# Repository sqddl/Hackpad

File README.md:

# Hackpad

### Overview
This hackpad is meant to be used for convience hence the layout of 4 keys per row. Making it ideal to rest your hand on it.
I wanted to make this so I can have specific keys for different functions for my computer.

BOM:
- 8x Cherry MX Switches
- 8x Blank DSA Keycaps
- 1x XIAO RP2040
- 4x M3x16 Screws
- 3D Printed Case (2 Parts)

| PCB | Schematics | Case |
|-----|------------|------|
|||

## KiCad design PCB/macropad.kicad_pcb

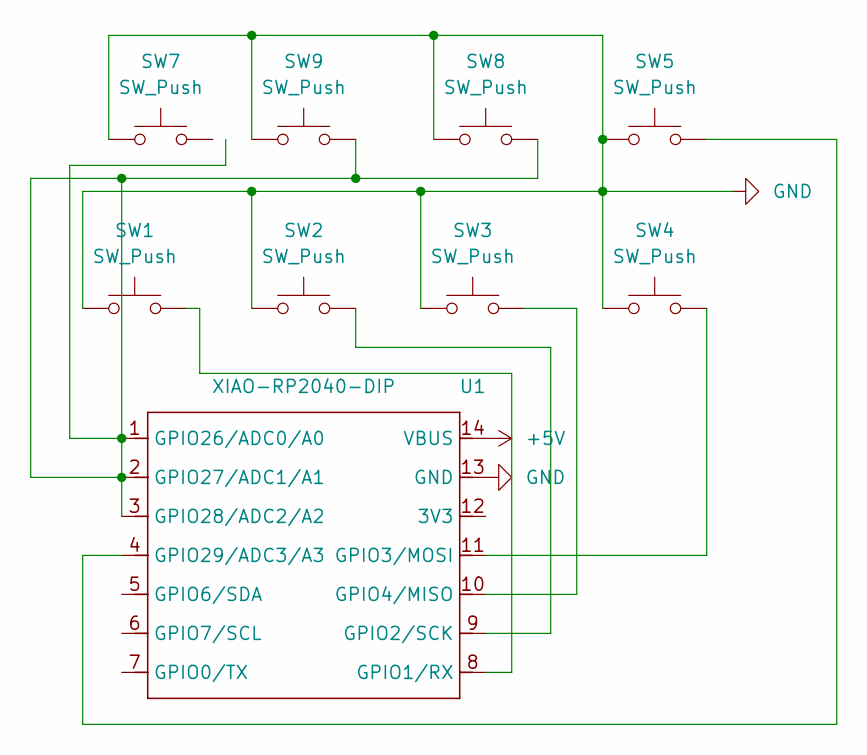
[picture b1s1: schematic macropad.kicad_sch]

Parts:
SW1, SW2, SW3, SW4, SW5, SW7, SW8, SW9: SW_Push; SW_Cherry_MX_1.00u_PCB
U1: XIAO-RP2040-DIP

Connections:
+5V: U1.14 (VBUS)
GND: SW1.1, SW2.1, SW3.1, SW4.1, SW5.1, SW7.1, SW8.1, SW9.1, U1.13 (GND)
unnamed: SW1.2, U1.8 (GPIO1/RX)
unnamed: SW2.2, U1.9 (GPIO2/SCK)
unnamed: SW4.2, U1.11 (GPIO3/MOSI)
unnamed: SW3.2, U1.10 (GPIO4/MISO)
unnamed: SW8.2, SW9.2, U1.1 (GPIO26/ADC0/A0), U1.2 (GPIO27/ADC1/A1), U1.3 (GPIO28/ADC2/A2)
unnamed: SW5.2, U1.4 (GPIO29/ADC3/A3)

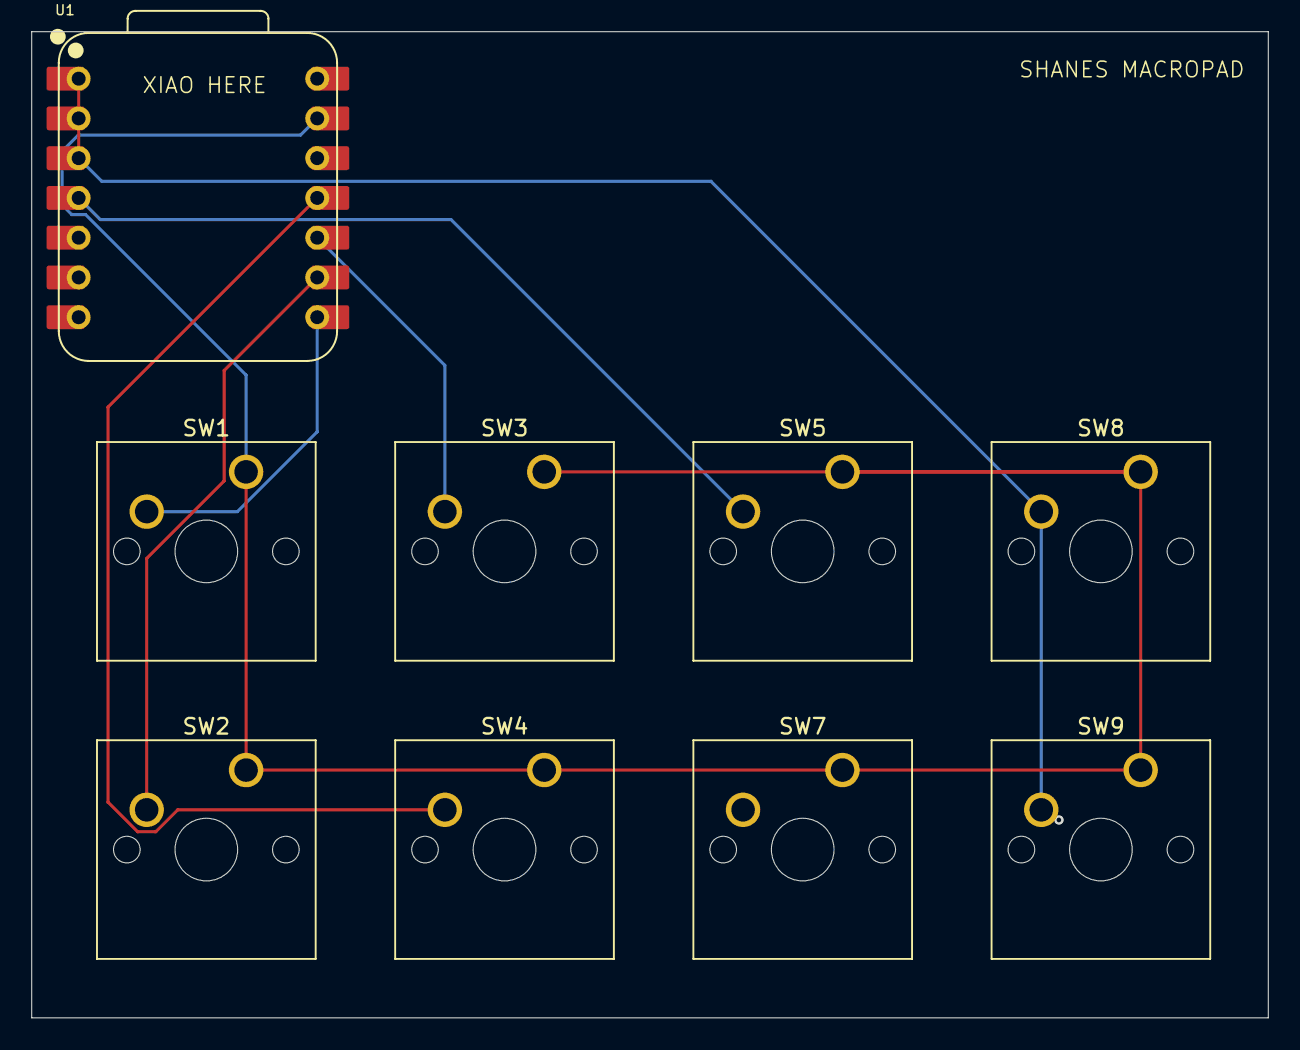
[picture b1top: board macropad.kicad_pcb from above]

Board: 2 copper layers, 79.0 x 63.0 mm, 9 parts (0 on the bottom side), 7 nets.

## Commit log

2025-12-23 Create S
2025-12-29 Implement keyboard polling in main loop
    Added keyboard polling in the main loop.
2025-12-29 Format and clean up main.py code
